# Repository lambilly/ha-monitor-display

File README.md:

# HA Monitor Display

ESP32-S3 电池供电的家庭信息屏：3.5" 触摸屏跑 ESPHome + LVGL，显示 Home Assistant 的家庭概览 / 网络 / 系统三页数据。本仓库提供两条数据通道的版本——**Native API 拉取（v0.9.0）** 与 **MQTT 推送（v1.x，推荐）**；屏幕通知页（Notify v2.0）开发中。

## 功能一览

- **三页信息 + 底部 TAB 触摸导航**（家庭 → 网络 → 系统）
  - 家庭页：电器 / 能耗 / 天气 / 居家模式（含音量、活动轨迹）/ 车位（状态 + 两辆车距离）
  - 网络页：网络总览 / NAS 运行 / 四路风扇（转速、温度、分档着色）/ 低电量
  - 系统页：CPU / 内存 / 存储三列指标、网络参数（RSSI / SIGQ / MQTT / WiFi）、SSID 与 IP、当前时间
- **熄屏休眠**：可调超时（15~900 s），触摸即醒；亮度滑块 + 断电记忆
- **每页背景色 8 档可调**（v1.1.0 起，HA 下拉选择，石墨 / 深红 / 深黄 / 墨绿 / 浅蓝 / 深蓝 / 深紫 / 深靛）
- 白字 + 图标承担配色的统一视觉规则；动态语义色（涨跌 / 居家模式 / 车位 / 风扇分档 / 信号分档 / 告警）保留

## 整机实拍

| 家庭页 | 网络页 |
| --- | --- |
|  |  |
| **系统页** | **通知页** |
|  |  |

## 硬件

| 项目 | 规格 |
| -- | -- |
| 主控 | ESP32-S3 N16R8（16MB Flash + 8MB octal PSRAM） |
| 屏幕 | 3.5" ST7796S 320×480，SPI（物理横屏 480×320，固件按竖装 320×480 + rotation 270） |
| 触摸 | FT6336U 电容触摸，I2C 地址 0x38 |
| 供电 | 锂电池（实测熄屏待机约 20 mA） |

关键引脚：SPI `clk=12 / mosi=11 / miso=13`，屏幕 `cs=10 / dc=9 / rst=8`，背光 PWM `15`，触摸 I2C `scl=6 / sda=7 / rst=5`。
⚠️ GPIO35/36/37 被 octal PSRAM 占用不可用；GPIO26~32 接 Flash。详细接线（含 TF 卡槽预留、CTP_INT 说明）见 `硬件焊接接线指南.md`。

## 版本线

| 版本 | 发布包 | 数据通道 | 说明 |
| -- | -- | -- | -- |
| **API v0.9.0** | `HA Monitor Display API v0.9.0.zip` | ESPHome Native API 拉取 + MQTT/TLS 8883 远程（双通道） | 2026-10-29 快照，前身版本 |
| **Mqtt v1.0** | `HA Monitor Display Mqtt v1.0.zip` | HA 每 5 s `mqtt.publish` 推送 JSON | MQTT 线首个定版 |
| **Mqtt v1.0.1** | `HA Monitor Display Mqtt v1.0.1.zip` | 同上 | 观感与数据修正累积 |
| **Mqtt v1.1.0** | `HA Monitor Display Mqtt v1.1.0.zip` | 同上 | 背景色 8 档 + 白字规则等大改 |
| **Mqtt v1.1.1** | `HA Monitor Display Mqtt v1.1.1.zip` | 同上 | 续航优化，**当前推荐**，v2.0 前回退基线 |
| Notify v2.0 | 开发中 | MQTT + Node-RED 清洗链 | 屏幕通知页，发布名 `HA Monitor Display Notify v2.0` |

各版本详细变更见 [CHANGELOG.md](CHANGELOG.md)。

## 快速开始（MQTT 版 v1.1.1，推荐）

### 1. 准备 MQTT broker

任选 Mosquitto / EMQX。局域网 1883 即可跑通；走外网务必上 8883 + TLS（方案见 `项目外网MQTT方案说明.md`）。主题约定：

```
home/ha-monitor-display          数据帧（retain, QoS1，HA → 屏幕）
esphome/ha-monitor-display/...   设备侧前缀（日志等）
```

### 2. 写 `secrets.yaml`（与主配置同目录）

```yaml
wifi_ssid: your-wifi
wifi_password: your-wifi-password
ap_password: your-fallback-ap-password
api_key: "运行 esphome 时自动生成，或自填 32 字节 base64"
mqtt_broker: your-mqtt-broker-address   # 例如 home.example.top
mqtt_port: 1883                         # 明文 MQTT 默认 1883
mqtt_username: your-mqtt-username
mqtt_password: your-mqtt-password
web_password: your-web-password
```

> Mqtt 版主配置的 broker 地址与用户名同样走 `!secret`（`mqtt_broker` / `mqtt_username`），
> 上面模板已含全部 9 项。无线 OTA **不需要单独的密码**：`ota:` 会自动复用 `api_key`
> 的加密密钥（ESPHome 强制两者一致）。

### 3. 部署文件

```
/config/esphome/
├── ha-monitor-display.yaml      主配置
├── ui_ha_monitor/               page_dashboard / page_network / page_system / page_notify
│                                tab_bar / ui_common
├── include/                     notify_store.h / notify_charset.h
└── fonts/                       NotoSansSC-SemiBold.ttf + materialdesignicons-webfont.ttf
/config/packages/
├── monitor_display_push.yaml    HA 侧 5 秒推送自动化
└── monitor_display_control.yaml 远程控制（屏幕带出门也能调亮度/熄屏/开关）
```

### 4. 编译烧录 + 启用自动化

ESPHome 里 Install（USB 首次，之后可 OTA）；在 HA 里重载自动化，确认 `packages` 已在 `configuration.yaml` 启用。设备上线后即可看到三页数据（5 s 一刷）。

## 快速开始（API 版 v0.9.0）

适合完全跑在局域网内、不想配 broker 的场景：数据由 ESPHome 通过 Native API 从 HA **主动拉取**（`platform: homeassistant` 传感器，51 处 entity_id），MQTT/TLS 8883 仅作远程备用通道。

1. 发布包解压后，`ha-monitor-display.yaml` 放 `/config/esphome/`，4 个 `page_*/ui_*` 放 `ui_ha_monitor/`，`fonts/` 同级
2. `secrets.yaml` 模板同上（`mqtt_host` / `mqtt_password` 不用 broker 时可留占位）
3. **把主配置里的 `entity_id` 改成你家 HA 的实际实体**——这 51 处是按我家设备命名的（如 `sensor.lamnas_ws_cpu_utilization_total`）
4. 编译烧录后数据即拉即显（刷新率由各 sensor 的 `update_interval` 决定）

## 目录结构

```
ha-monitor-display.yaml     主配置（板型 / WiFi / MQTT / API / 屏 / 触摸 / 休眠 / LVGL 全局）
ui_ha_monitor/              四个页面 + ui_common（字体/globals/公共件）+ tab_bar 底部导航
                              （墙屏专用；口袋版 pocket-homeassistant 用 ui_pocket/，两者不共用）
include/                    notify_store.h 通知环形缓冲/折行/清洗 + notify_charset.h 通知字库表（v2.0）
ha/                         HA 侧资源（→ /config/packages/ 部署）：
                              monitor_display_push.yaml     5 秒推送自动化（MQTT 版专用）
                              monitor_display_control.yaml  远程控制 5 实体（v2.1）
                              NR子流程-屏幕推送.json         Node-RED「屏幕推送」子流程导出（导入 NR 用）
fonts/                      中文字体 + MDI 图标字体
docs/                       方案文档：v2.0 NOTIFY 方案 / 外网 MQTT/TLS 方案与踩坑
hardware/                   硬件焊接接线指南 + 整机照片（正面 / 背面）
tools/                      monitor-display-generator.html  3.0 配置生成器（单文件，
                              放 /config/www/ 经 /local/ 打开；填 MQTT/WiFi + 选 51 槽位
                              实体 → 输出 secrets.yaml 与填好的推送包，支持连 HA 拉实体）
IP5406/                     5V UPS 电源板子项目（KiCad 工程 + BOM + 下单指引）：
                              25×16mm、IP5406 常开输出、拔插即换 IP5306 模块；
                              工程由 KiCad/gen_kicad.py 生成，改需求改脚本别手改 PCB
releases/                   历史发布包（GitHub Release 已挂对应 zip）
CHANGELOG.md                更新日志
```

> 仓库内 YAML 平铺在根目录；发布包（zip）里按 `ui_ha_monitor/` 子目录组织，解压即用（2026-11-12 目录拆分起；更早的包仍是 `ui/`）。

## 数据流（MQTT 版）

```
HA 自动化（每 5s，Jinja 组装 50 实体 JSON）
        │ mqtt.publish  →  home/ha-monitor-display (retain, QoS1)
        ▼
ESP32 mqtt.on_json_message ─▶ hd_* globals ─▶ LVGL 三页刷新
```

- 屏幕判"HA 离线"用数据新鲜度（>15 s 无新帧），不依赖 WiFi 状态
- 设备侧全局变量统一 `hd_*` 前缀；开关三态（null 显示 `--`）

## 远程控制（v2.1）

屏幕被带到公司/酒店时，**Native API 那条控制线会断**（HA 连不到设备，设备没有公网 IP），
而 MQTT 是设备主动往外连，所以数据一直好、控制全废。v2.1 把这 5 项也挂到 MQTT 上：

设备名固定 **HMD Remote**（MQTT 集成），实体名不带前缀——HA 会把设备名并进 entity_id，
最终得到 `number.hmd_remote_brightness` 这类干净结果，同时与 ESPHome 设备天然区分。

| HA 实体（`ha/monitor_display_control.yaml`） | entity_id | 下发主题 | 取值 |
| -- | -- | -- | -- |
| Screen Power | `light.hmd_remote_<...>` | `.../cmd/light` | `ON` / `OFF`（开=唤醒到上次亮度） |
| Brightness | `number.hmd_remote_<...>` | `.../cmd/bright` | 10 ~ 100 (%) |
| Sleep Timeout | `number.hmd_remote_<...>` | `.../cmd/sleep` | 15 ~ 900 (s) |
| Auto Sleep | `switch.hmd_remote_<...>` | `.../cmd/autosleep` | `ON` / `OFF` |
| Notify Wake | `switch.hmd_remote_<...>` | `.../cmd/wake` | `ON` / `OFF` |

设备把当前值 retain 回发到 `esphome/ha-monitor-display/state`：

```json
{"light":true,"bright":60,"sleep":300,"autosleep":true,"wake":false}
```

- 主题全 retain + QoS1：设备重连/重启会重放 HA 最后一次下发的值，**重启后以 HA 侧为准**
- 局域网时原生 API 那套和这套并存（名字带「远程」前缀），出门后只剩这套能用

## 功耗实测（真机，v1.1.1）

| 状态 | 电流 |
| -- | -- |
| 熄屏待机（60% 亮度 / 5s 推送 / modem-sleep） | **≈ 20 mA** |
| 亮屏 | ≈ 150~180 mA（每亮 1 分钟 ≈ 3 mAh） |

续航推算：500 mAh ≈ 21 h，1000 mAh ≈ 42 h，18650 3000 mAh ≈ 一周。

## 开发注意事项（踩过的坑）

- **中文字库是白名单制**：所有 `text:` 与 lambda 字符串里出现的汉字必须在字体 `glyphs` 里，改文案后要补字（有配套缺字扫描脚本）
- 字号三档 12 / 16 / 20（NotoSansSC-SemiBold），配 16px 文字的 MDI 图标用 20px 字体 + label 高 18，否则偏小偏上
- LVGL v9 的 label 未显式给宽度时是 `SIZE_CONTENT`（宽度随文本），依赖固定宽度的布局必须显式 `width`
- ESPHome `logs:` 的 tag 级别不能比全局 `level` 更细；`!include` 相对包含文件所在目录
- broker 走 1883 明文仅限局域网调试，外网务必 8883 + TLS

## 文档索引

- [CHANGELOG.md](CHANGELOG.md) — 各版本更新日志
- `硬件焊接接线指南.md` — 接线、排针定义、焊接顺序
- `项目外网MQTT方案说明.md` — 外网 MQTT/TLS 方案（DDNS / 端口映射 / 证书）
- `v2.0-NOTIFY方案.md` — 通知页设计稿（开发中）

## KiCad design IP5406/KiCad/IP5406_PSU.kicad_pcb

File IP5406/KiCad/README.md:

# IP5406 / IP5407 5V 电源板 — KiCad 工程说明（rev 1.5 定稿）

**25.00 × 16.00 mm** 两层板，与原 IP5306 模块**同尺寸、同引脚顺序**，可直接拔插替换。

- 右侧 J1（6 针 2.54）+ 左侧 J2（4 针 2.54）+ 板底 J4（2 针 2.54），**十二根针全部落在同一个 2.54 mm 网格上**，整板可插标准洞洞板
- 板底右侧新增 **J3 = PH2.0 电池母座**，电池包直接插拔
- 板上不放贴片 LED，电量灯从 J2-3 / J2-4 外接

---

## 1. 文件清单

| 文件 | 说明 |
|---|---|
| `IP5406_PSU.kicad_pro` | KiCad 工程文件，**双击这个打开** |
| `IP5406_PSU.kicad_sch` | 原理图（网络标签式画法，自包含符号库，无缺库风险） |
| `IP5406_PSU.kicad_pcb` | PCB（全部网络已布通，DRC 干净） |
| `IP5406_PSU.kicad_dru` | 自定义规则：铜到板边 0.2 mm（嘉立创工艺下限，见第 6 节） |
| `gerber/` | Gerber + 钻孔文件，可直接上传嘉立创下单 |
| `bom.csv` | 物料清单（自动导出） |
| `BOM_full.csv` | 完整物料清单（含封装/规格/数量） |
| `schematic.pdf` / `pcb_layout.pdf` / `pcb_copper.pdf` | 原理图、顶层装配、双面铜预览 |
| `netlist.net` | 网表（与 PCB 网络完全一致，已验证） |
| `drc.json` | DRC 报告（当前 0 违规 / 0 未连接） |
| `gen_kicad.py` | 生成本工程的脚本，改参数后重跑即可再生成 |

打开方式：KiCad 10 → 文件 → 打开工程 → 选 `IP5406_PSU.kicad_pro`。
（用 KiCad 10.0.6 生成并校验；KiCad 9 打开时会提示升级格式，允许即可。）

---

## 2. 关键尺寸（全部对 2.54 网格）

| 项目 | 数值 | 说明 |
|---|---|---|
| 板框 | **25.00 × 16.00 mm** | 与原 IP5306 模块完全一致 |
| J1（右排 6 针）x | 123.93 | 距右板边 1.07 mm |
| J2（左排 4 针）x | 101.07 | 距左板边 1.07 mm |
| **J1 ↔ J2 间距** | **22.86 mm = 9 × 2.54** | 插洞洞板跨 9 个孔距 |
| 排内针距 / 孔径 / 焊盘 | 2.54 mm / 1.0 mm / 1.6 mm | 标准 2.54 排针 |
| J1 针 y | 101.65 / 104.19 / 106.73 / 109.27 / 111.81 / 114.35 | 上下各留 1.65 mm |
| J2 针 y | 104.19 / 106.73 / 109.27 / 111.81 | 与 J1 的 2~5 号针同处网格行 |
| **J4 针（x / y）** | **103.61 / 106.15 ，114.35** | **两针均落在 2.54 网格**，与 J1/J2 同网格 |
| J3（PH2.0 座）针 | 116.40 / 118.40 ，114.20 | 2.0 mm 间距（电池母座，不参与洞洞板焊接） |

**边距为什么是 1.07 mm**：板宽 25 mm 要同时满足"两排针落在 2.54 网格上"，
可选间距只能是 2.54 的整数倍：9 × 2.54 = 22.86（两侧余 2.14 mm），
10 × 2.54 = 25.4 已超出板宽。所以 22.86 mm 是唯一解，两侧各 1.07 mm。
焊盘 1.6 mm 时铜到板边 0.27 mm、孔到板边 0.57 mm，均在嘉立创工艺范围内。

> 插洞洞板时：J1 六针 + J2 四针 + J4 两针共 **12 个脚全部落孔**，横向占 9 个孔距。

---

## 3. 板级接口

**J1（右侧 6 针，与原 IP5306 模块完全一致，从上到下）**

| 序号 | 丝印 | 功能 |
|---|---|---|
| 1 | OUT-5V | 5V 输出正（来自 J4 开关座） |
| 2 | GND | 公共地 |
| 3 | BAT | 锂电池正极（3.7–4.2 V），与 J3-1 并联 |
| 4 | GND | 公共地 |
| 5 | GND | 公共地 |
| 6 | VIN | 5V 充电输入正（4.65–6 V） |

> 板上只有这一处 VIN / GND 功率针，左侧 J2 不再引出 VIN/GND。

**J2（左侧 4 针备用排针，从上到下）**

| 序号 | 丝印 | 功能 | 用途 |
|---|---|---|---|
| 1 | DCP | 芯片 DCP 脚（已连通到 U1-2，默认不接） | 预留测试点 |
| 2 | KEY | 芯片 KEY 脚 | 接 10K NTC 做电池温度保护，或接按键 |
| 3 | LED1 | 电量 LED 驱动 1 | 外接电量灯（见第 4 节） |
| 4 | LED2 | 电量 LED 驱动 2 | 外接电量灯（见第 4 节） |

**J4（2 针 2.54 通孔，板底左侧，**已卡 2.54 网格**）**
外接电源开关座，串在 VOUT 与 OUT_SW 之间。

- **pin1 = VOUT**（芯片侧，5V 常出），坐标 (103.61, 114.35)
- **pin2 = OUT_SW**（负载侧，接 J1-1），坐标 (106.15, 114.35)
- 插开关 = 可控通断；插 **2.54 短接帽** = 常输出（默认用法）
- 两针与 J1/J2 处于同一 2.54 网格 → 本板插到别的 2.54 底板上时，J4 也能同时落孔
- 距下板边 1.65 mm，短接帽/开关不干涉

**J3（PH2.0 电池母座，板底右侧）**

- pin1 = BAT（坐标 116.40, 114.20）、pin2 = GND（118.40, 114.20），**2.0 mm 间距**
- 与 J1-3(BAT)、J1-4/5(GND) 并联，**电池包直接插拔**，不用再焊线
- 座体朝板外（−y 方向）伸出板边，插头从板下方水平插入，几乎不占板面
- 两个固定脚建议一起焊到 GND（座子外壳接地，抗插拔受力）
- 注意：J3 是 2.0 mm 间距，**不在 2.54 网格上**；插洞洞板时只焊 J1/J2/J4 的针即可

---

## 4. 外接电量灯怎么接（J2-3 / J2-4）

板上不放贴片 LED，电量指示从 J2 引出。IP5406 的 LED1/LED2 是**开漏驱动脚**，
两灯模式下用**两颗 LED 反并联**跨接：

```
        ┌──────── J2-3  (LED1)
        │
       ─┴─►│──  D1  (阳极接 LED1，阴极接 LED2)  = 低电量档
        │
       ─┬─◄│──  D2  (阳极接 LED2，阴极接 LED1)  = 高电量档
        │
        └──────── J2-4  (LED2)
```

- **D1**：阳极 → J2-3(LED1)，阴极 → J2-4(LED2)
- **D2**：阳极 → J2-4(LED2)，阴极 → J2-3(LED1)
- 两只方向相反，芯片交替拉低其中一脚点亮对应的一颗，实现两档电量指示
- 3 mm/5 mm 直插 LED 或 0805 贴片 LED 都行，飞线到 J2-3 / J2-4 即可
- 若只要"有电就亮"一颗灯：LED 阳极经 1 kΩ 接 BAT（或 5V），阴极接 LED1，
  另一脚 LED2 悬空

> 用 IP5407 标准品（默认 4 灯配置）时，两灯反并联可能显示不符预期，
> 这时按数据手册 Figure 1 的四灯结构外接，或直接不接指示灯。

---

## 5. 电路连接（已验证网表）

| 网络 | 连接 |
|---|---|
| VIN | U1-1(VIN)、C1-1、J1-6 |
| BAT | U1-6(BAT)、L1-2、C2-1、**J1-3**、**J3-1** |
| SW | U1-7(SW)、L1-1 |
| VOUT | U1-8(VOUT)、C3-1、C4-1、C5-1、**J4-1** |
| OUT_SW | **J4-2**、J1-1 |
| GND | U1-9(PAD)、C1/C2/C3/C4/C5-2、J1-2/4/5、**J3-2** |
| KEY | U1-3、J2-2 |
| LED1 | U1-4、J2-3 |
| LED2 | U1-5、J2-4 |
| DCP | U1-2、J2-1（已连通，两端默认都不接负载，等效悬空） |

---

## 6. PCB 状态（rev 1.5 复检）

- 板框：25.00 × 16.00 mm，2 层，1.5 mm 厚
- 元件：**11 个**（U1、L1、C1–C5、J1、J2、J3、J4；无贴片 LED）
- 布线：**全部网络布通，ratsnest = 0**，过孔 10 个、走线 54 段
  - **F.Cu**：SW / VOUT 干线与电容支路 / BAT（U1→L1→C2）/ **DCP**（U1-2 → J2-1）/
    KEY / LED1 / LED2 / **OUT_SW 全程**（J4-2 → y=111.7 → x=122.5 竖直 → J1-1）/ GND 缝合焊盘
  - **B.Cu**：GND 整层铺铜 / VOUT → J4-1（x=103.2 左通道 → y=113.2）/
    VIN（x=102.4 → 底边 y=115.6 → 斜进 J1-6）/ BAT 到 J3（x=113.25 下落 → y=112.8）/
    BAT 到 J1-3（via 后 y≈107.5 到 J1-3）
- DRC：**0 违规、0 未连接**（按 0.2 mm 最小间隙 / 0.2 mm 铜到板边 / 0.6 mm 丝印字高
  的实际工程规则复检）；ERC：**0 违规**；网表 ↔ PCB **10 个网络全部一致**
- **OUT_SW 之所以走顶层**：它必须从板左侧横穿到 J1-1，走底层会把 GND 铺铜切成
  东西两块，J1 的 GND 针会变成孤岛。移到顶层后底层铺铜完整，J1-2/4/5 直接
  连到铺铜，不需要额外桥接线
- 板边规则：`IP5406_PSU.kicad_dru` 把"铜到板边"约束设为 **0.2 mm**（嘉立创下限），
  因为 25 mm 宽 + 2.54 网格排针必然让焊盘铜皮距边 0.27 mm

## 6.1 正面丝印装配标记（rev 1.5 新增）

全部在 **F.Silkscreen**（正面），线宽 0.12 mm，字高 0.65–0.70 mm。板子从正面看时：

| 标记 | 位置 / 内容 | 说明 |
|---|---|---|
| **U1 本体框** | x 107.75–111.85，y 105.70–110.70 | ESOP8 本体轮廓，**左上角削角 0.7 mm = 缺口标志** |
| **U1 pin1 点 + "1"** | 实心圆点 (108.25, 105.30)、数字 "1" (109.15, 105.05) | 都在本体框**外面**，芯片焊好后仍看得见；削角 + 圆点都指向 **pin1 = VIN（左上）**，右上角是 pin8 = VOUT |
| **L1 本体框** | x 113.60–118.80，y 105.50–109.30 | 电感轮廓，左上角同样削 0.5 mm 缺口，指向 **pad1 = SW（左侧）**；电感本身无极性，缺口只用于对齐方向 |
| **C1 / C3 / C4 极性** | "+" 在 pad1 正上方（x = 103.7 / 110.3 / 113.7，y = 101.45），"−" 在 pad2 正上方（x = 105.5 / 112.1 / 115.5） | pad1 = VIN 或 VOUT 正端，pad2 = GND |
| **C2 极性** | "+" (119.50, 110.75)、"−" (121.30, 110.75) | pad1 = BAT 正端，pad2 = GND；在电容下方避开上方 BAT 走线 |
| **J3 极性** | "+" (116.40, 112.75)、"−" (118.40, 112.75) | PH2.0 电池母座 pad1 = BAT+、pad2 = GND−，插电池前先看这两个符号 |
| **C5 不标** | 100nF MLCC 无极性 | 刻意不画 +/-，避免误导 |
| 背面丝印 | B.Silkscreen | J1 六针名称（OUT-5V/GND/BAT/GND/GND/VIN）+ 标题 `IP5406 5V UPS / Lambilly @2026.11` |

> 贴片 MLCC（0805）本身无极性，"+" 只是标明该焊盘接的是电源正端（VIN/VOUT/BAT），
> 方便用万用表核对；如果换成钽电容/电解电容，就按 "+" 装，不要再对调。
> 单看丝印检查芯片方向：**缺口 + 圆点 = pin1（VIN）那一角**，与 J1-6 (VIN) 同一侧。

---

## 7. 芯片兼容性（重要）

**IP5406 与 IP5407 引脚完全相同**（官方数据手册 Pin definition 一致）：

| 引脚 | 名称 | 功能 |
|---|---|---|
| 1 | VIN | 5V 充电输入 |
| 2 | DCP | USB-A D+/D- 识别（不用则悬空） |
| 3 | KEY | 按键 / 照明灯 / NTC 复用 |
| 4 | LED1 | 电量 LED 驱动 |
| 5 | LED2 | 电量 LED 驱动 |
| 6 | BAT | 电池正极 |
| 7 | SW | DC-DC 开关（接电感） |
| 8 | VOUT | 5V 升压输出 |
| 9 (PAD) | GND | 散热焊盘接 GND |

→ **本板 IP5406 / IP5407 / IP5406T 通用**，直接换芯片即可，无需改板。

**与 IP5306 不同**（不能直接互换芯片，控制脚 2~5 定义不同）：

| 引脚 | IP5306 | IP5406 / IP5407 |
|---|---|---|
| 1 | VIN | VIN ✅ |
| 2 | LED1 | DCP ❌ |
| 3 | LED2 | KEY ❌ |
| 4 | LED3 | LED1 ❌ |
| 5 | KEY | LED2 ❌ |
| 6/7/8 | BAT/SW/VOUT | 相同 ✅ |

详见《IP5406电源板设计方案.md》第 9 章。

---

## 8. 打样与装配

1. 嘉立创下单：2 层、1.5 mm、1 oz 铜、喷锡（HASL），直接上传 `gerber/` 里的
   8 个层文件 + 1 个 job 文件 + 1 个钻孔文件（`IP5406_PSU.drl`），共 11 个
2. J1/J2/J4 孔径 1.0 mm、焊盘 1.6 mm、间距 2.54 mm；J3 孔径 1.0 mm、间距 2.0 mm
3. U1 为 ESOP8 带散热焊盘，建议 SMT；手焊需热风枪，**底部散热盘必须着锡并接 GND**
4. 装配顺序：先贴 U1/L1/电容 → 再焊 J1/J2 排针、J4、J3（PH2.0 座）
5. 上电顺序：先只接 5V 输入验 5V 输出 → 再接电池验充电 → 最后带载拔插测试
   （核心指标：不重启）
6. J4 不接开关时务必插短接帽，否则 5V 输出断开（芯片本身仍正常）

---

## 9. 修改工程

改 `gen_kicad.py` 里的坐标/元件参数，重跑：

```
"C:\Program Files\KiCad\10.0\bin\python.exe" gen_kicad.py
```

校验命令：

```
"C:\Program Files\KiCad\10.0\bin\kicad-cli.exe" sch export netlist --output n.net IP5406_PSU.kicad_sch
"C:\Program Files\KiCad\10.0\bin\kicad-cli.exe" pcb drc --format json --output drc.json IP5406_PSU.kicad_pcb
```

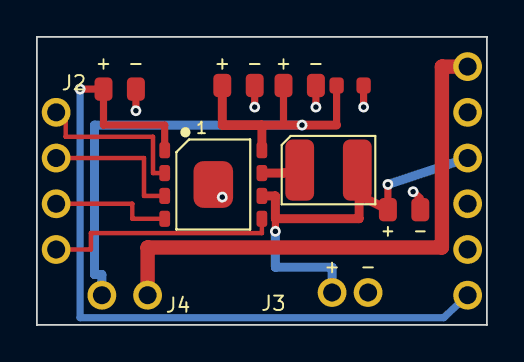
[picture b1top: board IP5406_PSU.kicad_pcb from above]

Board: 2 copper layers, 25.0 x 16.0 mm, 11 parts (0 on the bottom side), 10 nets.

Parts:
C1: 22uF; C1
C2: 10uF; C2
C3: 22uF; C3
C4: 22uF; C4
C5: 100nF; C5
J1: 6PAD; J1
J2: SPARE4; J2
J3: PH2.0; J3
J4: SW_JUMPER; J4
L1: 1uH/4A; L1
U1: IP5406; U1

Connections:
BAT: C2.1, J1.3, J3.1, L1.2, U1.6
DCP: J2.1, U1.2
GND: C1.2, C2.2, C3.2, C4.2, C5.2, J1.2, J1.4, J1.5, J3.2, U1.9
KEY: J2.2, U1.3
LED1: J2.3, U1.4
LED2: J2.4, U1.5
OUT_SW: J1.1, J4.2
SW: L1.1, U1.7
VIN: C1.1, J1.6, U1.1
VOUT: C3.1, C4.1, C5.1, J4.1, U1.8

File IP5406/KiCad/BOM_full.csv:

Ref,Qty,Value,Package,Note
U1,1,IP5406,ESOP8 (SOP-8 w/ thermal pad 3.9x4.9),IP5407 / IP5406T also fit (same pinout)
L1,1,1uH / 4A,5x5 or 6x6 mm shielded,<0.05 ohm DCR; "1R0" marking on the original module
C1,1,22uF / 10V,0805 X5R (0603 ok),VIN decoupling - close to U1 pin 1
C2,1,10uF / 10V,0805 X5R,BAT decoupling - close to L1 pad 2
C3,1,22uF / 10V,0805 X5R,VOUT bulk
C4,1,22uF / 10V,0805 X5R,VOUT bulk
C5,1,100nF / 16V,0603 X7R,VOUT high-frequency bypass
J1,1,2.54mm 6P THT,1x6 pin header / 6 through-hole pads,Same pinout + position as the IP5306 module
J2,1,2.54mm 4P THT,1x4 pin header,DCP / KEY / LED1 / LED2 spare header
J3,1,PH2.0 2P right-angle socket,PH2.0-2P (2.0mm pitch, body overhangs the edge),Battery pack plugs straight in; pin1=BAT pin2=GND
J4,1,2.54mm 2P THT,1x2 pin header (both pins on the 2.54 grid),External ON/OFF switch; fit jumper cap for always-on
JP1,1,Jumper cap 2.54mm,-,Optional: shorts J4 when no switch is used

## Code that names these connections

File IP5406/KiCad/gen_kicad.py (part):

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  J1 (right, 6 x 2.54 THT)  : OUT-5V / GND / BAT / GND / GND / VIN   (1:1 with IP5306 module)
  J2 (left,  4 x 2.54 THT)  : DCP / KEY / LED1 / LED2               (spare header)
  J4 (bottom, 2 x 2.54 THT) : VOUT / OUT_SW   (external switch or jumper, 2.54 grid)
  J3 (bottom right, PH2.0)  : BAT / GND       (battery socket, plug goes in horizontally)
  Row-to-row spacing        : 22.86 mm = 9 x 2.54 mm   (perfboard friendly)
  Edge margin               : 1.07 mm each side (25 - 9 x 2.54 = 2.14 mm)
  F.Silk assembly marks      : U1/L1 outlines + pin-1 notch, +/- on C1-C4, C2, J3
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LIB = []
LIB.append(rect_symbol(
    "IP5406_Lib:IP5406", "U",
    left_pins=[("1", "VIN"), ("2", "DCP"), ("3", "KEY"), ("4", "LED1"), ("9", "GND")],
    right_pins=[("8", "VOUT"), ("7", "SW"), ("6", "BAT"), ("5", "LED2")],
    width=10.16, height=12.7, show_names=True, body_text="IP5406"))
LIB.append(rect_symbol("IP5406_Lib:L", "L", [("1", "SW")], [("2", "BAT")],
                       width=6.35, height=5.08, show_names=True, body_text="1uH"))
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                       width=5.08, height=3.81, body_text="C"))
LIB.append(rect_symbol(
    "IP5406_Lib:Conn_01x06", "J",
    left_pins=[], right_pins=[("1", "OUT-5V"), ("2", "GND"), ("3", "BAT"),
                              ("4", "GND"), ("5", "GND"), ("6", "VIN")],
    width=5.08, height=15.24, show_names=True, body_text="6-PAD"))
LIB.append(rect_symbol(
    "IP5406_Lib:Conn_01x04", "J",
    left_pins=[], right_pins=[("1", "DCP"), ("2", "KEY"),
                              ("3", "LED1"), ("4", "LED2")],
    width=5.08, height=10.16, show_names=True, body_text="SPARE"))
LIB.append(rect_symbol("IP5406_Lib:Conn_01x02", "J",
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     [("1", "DCP"), ("2", "KEY"), ("3", "LED1"), ("4", "LED2")], False),
    ("J4", "SW JUMPER", "IP5406_Lib:Conn_01x02", 240.03, 96.52,
     [("1", "VOUT"), ("2", "OUT_SW")], False),
    ("J3", "PH2.0 BAT", "IP5406_Lib:Conn_01x02", 240.03, 116.84,
     [("1", "BAT"), ("2", "GND")], False),
]

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
notes = [
    (63.5, 160.02, "POWER PATH: VIN -> load + charge; unplug -> battery boost, seamless"),
    (63.5, 165.1, "5V OUTPUT ALWAYS ON (no light-load shutdown). DCP pin 2 -> J2-1."),
    (63.5, 170.18, "J4: external ON/OFF switch (2.54 grid); fit a jumper for always-on output."),
    (63.5, 175.26, "J2: DCP / KEY(NTC or button) / LED1 / LED2 = battery gauge LEDs."),
    (63.5, 180.34, "LEDs (external): 2 pcs anti-parallel between LED1 and LED2 (A/K crossed)."),
    (63.5, 185.42, "J3: PH2.0 battery socket (BAT/GND) - plug the pack in directly."),
    (63.5, 190.5, "F.Silk: U1/L1 outlines + pin-1 notch; +/- on C1-C4, C2, J3."),
]
for x, y, txt in notes:
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
# --- front-side assembly markings -------------------------------------------
# U1 (ESOP8): body outline with a chamfered top-left = pin-1 notch.
# Pin 1 = VIN (upper left), pin 8 = VOUT (upper right).  The dot and "1"
# sit just OUTSIDE the body so they stay visible after the chip is soldered.
silk_poly([(107.75, 106.40), (108.45, 105.70), (111.85, 105.70),
           (111.85, 110.70), (107.75, 110.70), (107.75, 106.40)])
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silk("+", 119.5, 110.75, size=0.65, center=True)   # C2 pad1 = BAT
silk("-", 121.3, 110.75, size=0.65, center=True)   # C2 pad2 = GND

# J3 PH2.0 battery socket: pad 1 = BAT+, pad 2 = GND-
silk("+", 116.4, 112.75, size=0.7, center=True)
silk("-", 118.4, 112.75, size=0.7, center=True)

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track("VOUT", [(113.7, 104.9), (113.7, 103.35)], 0.4)
track("VOUT", [(116.65, 104.9), (116.65, 103.15)], 0.4)

# BAT: U1 pin6 -> around L1 -> L1 pad2 -> C2 -> J1-3 / J3-1
track("BAT", [(112.5, 108.835), (113.25, 108.835)], 0.5)
track("BAT", [(113.25, 108.835), (113.25, 110.1), (117.9, 110.1),
              (117.9, 108.8)], 0.5)
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track("VIN", [(107.1, 106.295), (107.1, 104.9), (103.7, 104.9),
              (103.7, 103.55)], 0.4)

# DCP: U1 pin2 -> J2-1 (top layer, above KEY; runs between the VIN trunk and
# U1 pad1 without touching either)
track("DCP", [(107.1, 107.565), (106.45, 107.565), (106.45, 105.55),
              (101.6, 105.55), (101.6, 104.19), (101.07, 104.19)], 0.25)
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               (103.0, 111.81), (101.07, 111.81)], 0.25)

# ---- bottom layer ----
# VOUT -> J4 pin1 (down the left channel, then along y = 113.2)
via("VOUT", 114.73, 104.9)
track("VOUT", [(114.73, 104.9), (103.2, 104.9)], 0.5, pcbnew.B_Cu)
track("VOUT", [(103.2, 104.9), (103.2, 113.2), (103.61, 113.2),
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track("VIN", [(102.4, 102.9), (102.4, 115.6), (122.6, 115.6),
              (123.93, 114.35)], 0.4, pcbnew.B_Cu)

# OUT_SW: J4 pin2 -> across the board -> up the right channel -> J1-1
# (top layer: keeps the bottom GND pour in one piece, so J1's GND pads are
#  connected straight to it without a bridge)
track("OUT_SW", [(106.15, 114.35), (106.15, 111.7), (122.5, 111.7),
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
